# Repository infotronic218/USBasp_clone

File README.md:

# USBasp clone PCB design with Kicad

A simple projet for designing USBasp clone with Kicad 5.1.5 

## Schematic

## Routes View of the PCB

## 3D View of the PCB

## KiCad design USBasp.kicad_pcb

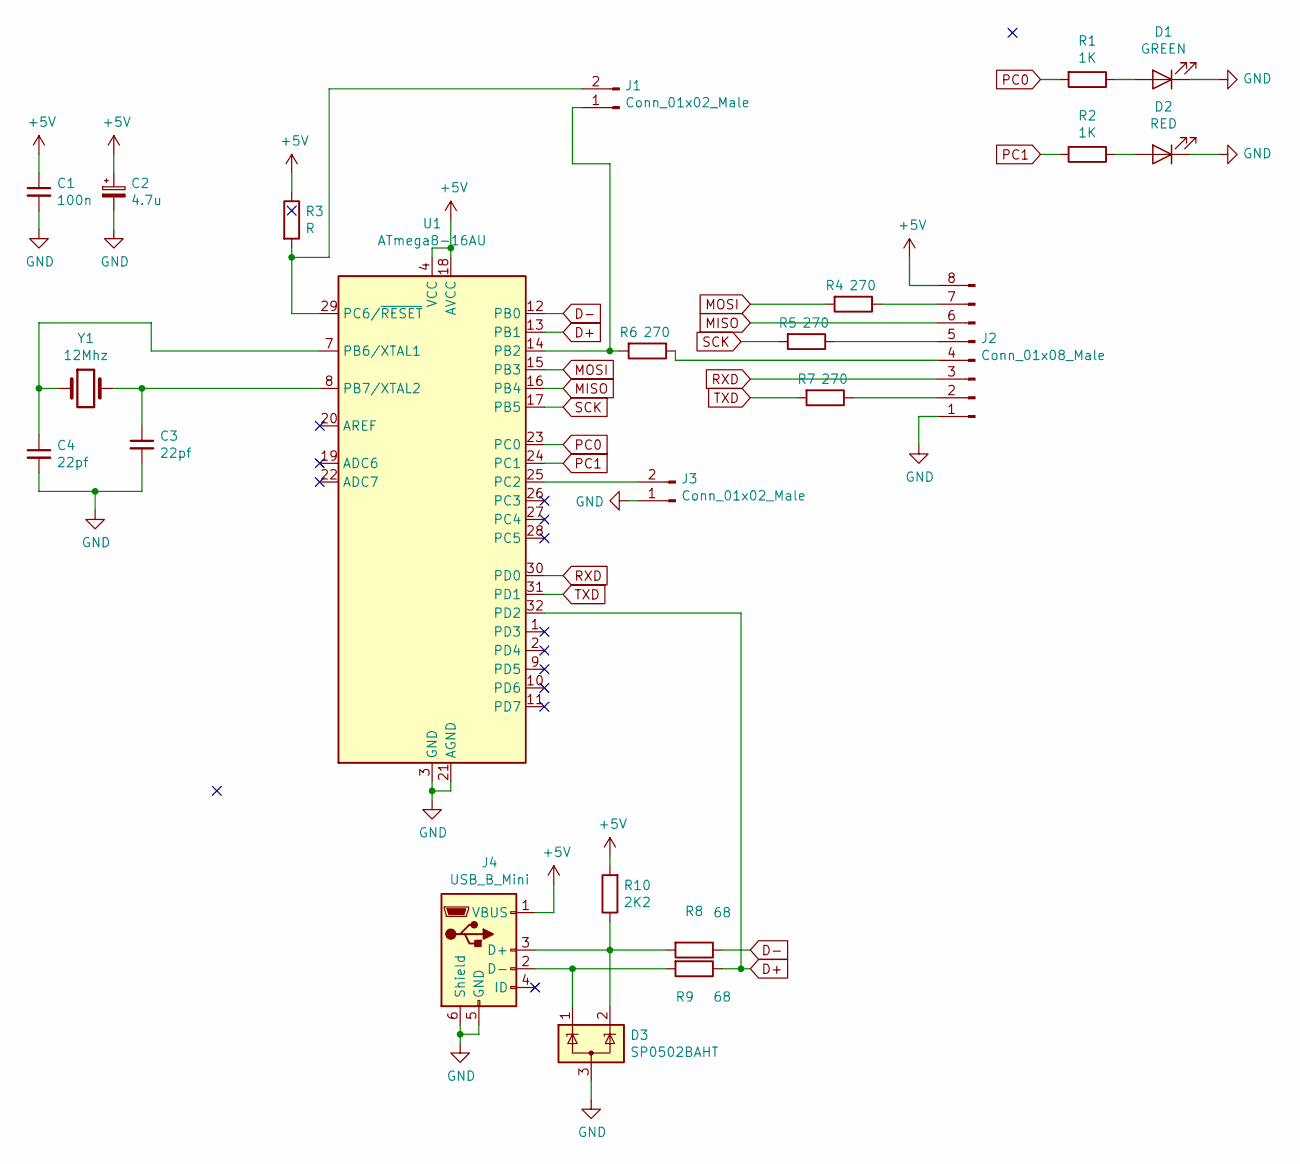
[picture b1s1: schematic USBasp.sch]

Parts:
C1: 100n; C_0603_1608Metric
C2: 4.7u; C_1206_3216Metric
C3, C4: 22pf; C_0603_1608Metric
D1: GREEN; LED_0805_2012Metric
D2: RED; LED_0805_2012Metric
D3: SP0502BAHT; SOT-23
J1, J3: Conn_01x02_Male; PinHeader_1x02_P2.00mm_Vertical
J2: Conn_01x08_Male; PinHeader_1x08_P2.00mm_Vertical
J4: USB_B_Mini; USB_Micro-B_GCT_USB3076-30-A
R1, R2: 1K; R_0603_1608Metric
R3: R; R_0603_1608Metric
R4, R5, R6, R7: 270; R_0603_1608Metric
R8, R9: 68; R_0603_1608Metric
R10: 2K2; R_0603_1608Metric
U1: ATmega8-16AU; TQFP-32_7x7mm_P0.8mm
Y1: 12Mhz; Crystal_HC49-4H_Vertical

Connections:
+5V: C1.1, C2.1, J2.8, J4.1 (VBUS), R3.1, R10.2, U1.4 (VCC), U1.6 (VCC), U1.18 (AVCC)
D+: R9.1, U1.13 (PB1), U1.32 (PD2)
D-: R8.1, U1.12 (PB0)
GND: C1.2, C2.2, C3.2, C4.2, D1.1 (K), D2.1 (K), D3.3 (A), J2.1, J3.1, J4.5 (GND), J4.6 (Shield), U1.3 (GND), U1.5 (GND), U1.21 (AGND)
MISO: J2.6, U1.16 (PB4)
MOSI: R4.2, U1.15 (PB3)
unnamed: C3.1, U1.8 (PB7/XTAL2), Y1.2
unnamed: C4.1, U1.7 (PB6/XTAL1), Y1.1
unnamed: D1.2 (A), R1.1
unnamed: D2.2 (A), R2.1
unnamed: D3.1 (K), J4.2 (D-), R9.2
unnamed: D3.2 (K), J4.3 (D+), R8.2, R10.1
unnamed: J1.1, R6.2, U1.14 (PB2)
unnamed: J1.2, R3.2, U1.29 (PC6/~RESET)
unnamed: J2.2, R7.1
unnamed: J2.4, R6.1
unnamed: J2.5, R5.1
unnamed: J2.7, R4.1
unnamed: J3.2, U1.25 (PC2)
PC0: R1.2, U1.23 (PC0)
PC1: R2.2, U1.24 (PC1)
RXD: J2.3, U1.30 (PD0)
SCK: R5.2, U1.17 (PB5)
TXD: R7.2, U1.31 (PD1)

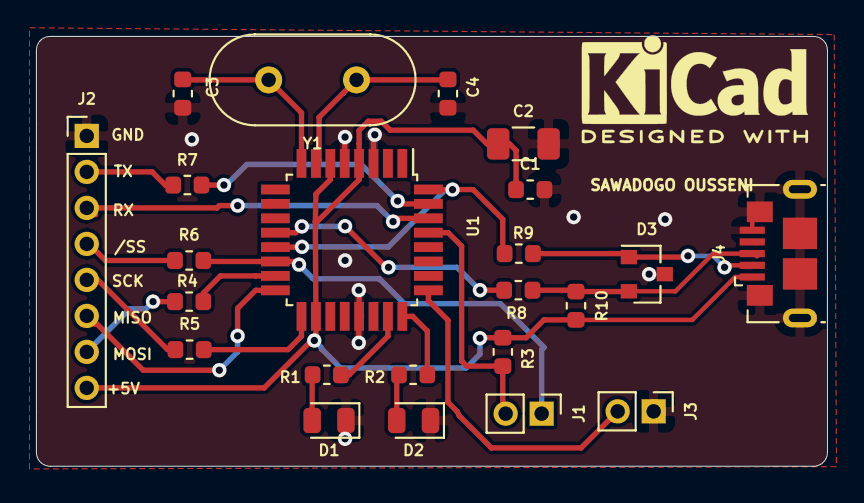
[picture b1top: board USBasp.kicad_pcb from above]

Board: 2 copper layers, 43.9 x 23.9 mm, 23 parts (0 on the bottom side), 24 nets.
